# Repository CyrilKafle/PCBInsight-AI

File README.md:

# PCBInsight AI

### PCB Design Review Platform

**[View the landing page →](https://cyrilkafle.github.io/PCBInsight-AI/)**

An AI-augmented engineering design review tool for KiCad PCB projects — a lightweight, local analog of the automated design-review tooling used inside hardware companies (NVIDIA, AMD, Apple, Intel). It does not replace KiCad's Design Rule Check (DRC); it sits a level above DRC, producing the kind of higher-level engineering judgment an experienced PCB reviewer would give in a design review: *why* something could be a problem, *what engineering principle* is involved, a *suggested fix*, a *severity*, and a *confidence level*.

Full design rationale, phased plan, and engineering-check catalogue: [`DESIGN.md`](DESIGN.md). Why the major architectural calls were made the way they were: [`docs/ENGINEERING_DECISIONS.md`](docs/ENGINEERING_DECISIONS.md). How the deterministic engine and the AI layer are each validated: [`docs/VALIDATION.md`](docs/VALIDATION.md).

## Status: Phase 4 complete — full local dashboard (FastAPI + React) with board visualization, AI chat, and PDF export

This is a from-scratch rebuild of what was previously a separate FPGA/PCB robotic-arm project. See [`DESIGN.md`](DESIGN.md) for the full phased plan and [`SKILLS_LOG.md`](SKILLS_LOG.md) for tools/concepts learned as the project progresses.

## What it does

1. **Parse** — drag-and-drop a full KiCad project (`.kicad_pcb`, `.kicad_sch`, netlist, project metadata); the parser builds an internal representation of components, nets, traces, vias, copper pours, footprints, and board dimensions.
2. **Analyze** — run dozens of deterministic engineering checks across routing, power, ground integrity, differential pairs, decoupling placement, component placement, manufacturability, thermal risk, and signal integrity.
3. **AI review** — send a *summarized structured digest* of the board (never raw PCB files) to Claude for a senior-engineer-style narrative review that explains and contextualizes what the deterministic checks found.
4. **Score** — compute an overall 0-100 engineering score plus subscores (routing, power, signal integrity, manufacturability, placement, thermals, documentation), color-coded green/yellow/orange/red.
5. **Report** — generate a professional HTML report (exportable to PDF) with an executive summary, board statistics, engineering metrics, warnings, recommendations, the AI review, and charts/visualizations.

## Screenshots

Real output from a live run against `examples/stm32_usb_dev` — including a real Claude review and a real grounded chat answer, not mockups.

<table>
<tr>
<td width="50%"></td>
<td width="50%"></td>
</tr>
<tr>
<td width="50%"></td>
<td width="50%"></td>
</tr>
</table>

More screenshots (PDF export, upload flow) on the [landing page](https://cyrilkafle.github.io/PCBInsight-AI/).

## Architecture

```
backend/    FastAPI service + CLI: parser, analysis engine, AI integration, HTML/PDF report generation
frontend/   React + TypeScript + Tailwind dashboard: upload, board visualization, issue browser, AI chat panel
examples/   Engineering Validation Corpus -- ten purpose-built KiCad boards, see examples/README.md
docs/       Architecture notes, screenshots, example reports
```

See [`DESIGN.md`](DESIGN.md) for the full architecture rationale and the catalogue of engineering checks.

## Project metrics

Real numbers, computed from the codebase as of this commit — not estimates:

| Metric | Value |
|---|---|
| Analysis categories | 9 |
| Deterministic checks | 28 |
| Unit tests (all passing, backend) | 159 |
| Lines of Python — `backend/app/` | 2,957 |
| Lines of Python — `backend/tests/` | 1,386 |
| Engineering Validation Corpus | 10 purpose-built boards, see `examples/README.md` |
| KiCad parser | Custom S-expression parser, 0 `pcbnew`/CAD dependencies |
| Supported input format | KiCad `.kicad_pcb` |
| Interfaces | CLI (`pcbinsight review`, single-board or batch-folder) and a local React/FastAPI web dashboard |
| AI model | Claude Sonnet 5 (narrative review layer only — never the analysis engine) |
| Report format | Self-contained HTML (embedded charts, no external assets) and downloadable PDF (ReportLab) |

## Running it

Both the CLI and the web dashboard are runnable today.

```sh
cd backend
pip install -r requirements.txt

# Analyze one board
python -m app.cli review ../examples/simple_board
# -> simple_board_report.html in the current directory

# Analyze every board in a folder (auto-detected batch mode)
python -m app.cli review path/to/boards/ --out reports/
# -> reports/<board-folder-name>/report.html for each, plus reports/summary.html

# Add --ai to also generate a Claude narrative review (requires ANTHROPIC_API_KEY)
python -m app.cli review ../examples/simple_board --ai

# Or install it as a real `pcbinsight` command:
pip install -e .
pcbinsight review ../examples/simple_board
```

```sh
# Web dashboard (local-only -- see DESIGN.md's "Public Positioning & Audience")

# Terminal 1: backend API
cd backend
uvicorn app.main:app --port 8000

# Terminal 2: frontend dev server
cd frontend
npm install
npm run dev
# -> open http://localhost:5173, drag in a KiCad project folder
```

## Roadmap

- **Phase 0 (done):** Hand-rolled S-expression parser for `.kicad_pcb` (no `pcbnew`/KiCad-install dependency), internal Pydantic board model, proven against an `examples/` fixture board with unit tests.
- **Phase 1 (done):** Deterministic engineering-check engine — all nine categories (routing, power, ground, differential pairs, decoupling, placement, manufacturability, thermal, signal integrity) implemented as independent `check(board) -> list[Issue]` modules, orchestrated by `app/analysis/run_all_checks`. 78 tests passing (24 parser + 54 analysis), each check proven on a synthetic bad-case board and silent on a clean one. Manufacturability intentionally covers only trace width / annular ring / via density — silkscreen-over-pad and copper-sliver checks are deferred since the board model doesn't yet capture silkscreen text geometry or full pour polygon shape.
- **Phase 2 (done):** Transparent scoring engine (`app/analysis/scoring.py` — severity-weighted deductions per subscore, overall = average) and a self-contained HTML report renderer (`app/reports/html_report.py`) with embedded matplotlib charts, color-coded score badges, and a full issues table. No AI dependency yet — see [`docs/example_report.html`](docs/example_report.html) for a real generated report off the `examples/simple_board` fixture. 93 tests passing.
- **Phase 3 (done):** AI Engineering Review Layer — `app/ai/summarizer.py` builds a structured digest (scores, a deterministically-computed evidence block, issue list, board statistics; never raw geometry) and `app/ai/review.py` sends it to Claude under a strict system prompt that forbids inventing findings and requires citing issue IDs (e.g. `PWR-004`, assigned by `run_all_checks`). Claude is a technical writer over the deterministic engine's output, never a second analysis engine. `answer_question()` grounds the (Phase 4) AI chat panel the same way. The digest carries a `schema_version`, and `find_unsupported_citations()` code-checks (not just prompt-asks) that any issue ID Claude cites actually exists, logging a warning otherwise. 115 tests passing, all using a dependency-injected fake Anthropic client — no live API key needed to prove the code is correct, since none was available in this environment. See `DESIGN.md`'s "AI Integration Architecture" section for the full spec.
- **CLI (done):** `app/cli.py` — `pcbinsight review <path>` runs the full parse → analyze → score → (optional AI) → report pipeline for one board, or auto-detects a folder of boards and batch-processes all of them into per-board reports plus a `summary.html` index. Installable as a real command via `backend/pyproject.toml`'s `[project.scripts]`. Batch mode catches per-board failures so one malformed `.kicad_pcb` doesn't abort the run. 120 tests passing.
- **Phase 4 (done):** Local-only FastAPI service (`POST /api/review` with streamed/size-capped uploads and a path-traversal guard; `POST /api/chat`; `POST /api/report/pdf`) plus a React/TypeScript dashboard: drag-and-drop/folder upload, color-coded score cards, searchable/filterable issue browser with expandable "why does this matter" detail, an **SVG board visualization** (outline, per-layer traces, vias, components, zoom/pan, layer toggles, clickable issue markers that cross-highlight the issue browser), a **net-length histogram** and **issue-by-category chart**, a **grounded AI chat panel** (reuses the Phase 3 `answer_question()`; fails gracefully without an API key), and **PDF export** (ReportLab, reusing the HTML report's charts). Verified end-to-end in a real browser against the running backend. 135 tests passing (backend).
- **Stretch:** multi-board comparison, revision history, BOM analysis, Altium/EasyEDA import support, plugin architecture (see `DESIGN.md` for the full stretch list, including the review-session workflow and Design Rule Authoring SDK).

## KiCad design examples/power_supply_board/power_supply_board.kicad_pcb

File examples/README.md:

# Engineering Validation Corpus

This is not a folder of demo files — it's a curated set of KiCad boards, each authored for a specific reason, that validates the parser, the deterministic analysis engine, the AI layer, and the dashboard end to end. Every board exists to prove something the others don't; there are no filler fixtures. See `docs/VALIDATION.md` for how to run the full validation flow (this corpus + `backend/scripts/validate_ai.py`) and how to interpret the results.

| Board | Primary purpose |
|---|---|
| `simple_board` | Parser smoke test — minimal hand-authored board exercising every S-expression construct the parser handles |
| `stm32_usb_dev` | Medium-quality realistic board — a substantial fixture for the analysis engine |
| `flawed_reference` | Deliberately poor board tripping nearly every check category at once |
| `high_quality_reference` | Clean reference board — demonstrates good engineering, the "everything's fine" counterpart to `flawed_reference` |
| `rf_clock_board` | Signal-integrity and differential-pair focus |
| `power_supply_board` | Power delivery and decoupling focus |
| `thermal_reference` | Thermal design focus |
| `manufacturing_reference` | DFM (manufacturability) focus |
| `parser_edge_cases` | Parser robustness — unicode, escaped quotes, hostile characters, not analysis-engine coverage |
| `mixed_realistic_board` | What an intermediate engineer's board actually looks like — mostly solid, a few realistic slips |

## simple_board

Hand-authored minimal two-layer board (`simple_board.kicad_pcb` + `.kicad_pro`) used as the Phase 0 parser fixture. Not a KiCad-exported file — written directly in KiCad's S-expression format to exercise every construct the parser needs to handle: board outline (`gr_rect` on `Edge.Cuts`), two copper layers, four footprints (`U1` MCU, `C1` decoupling cap, `R1` resistor, `J1` USB-C connector) covering the refdes-prefix classification table, three nets (`GND`, `+3V3`, `/SCLK`) with traces, a via, and a `GND` copper pour zone.

## stm32_usb_dev

A richer four-layer example board (`stm32_usb_dev.kicad_pcb` + `.kicad_pro`) — an STM32F103 USB dev board: MCU, AMS1117-3.3 LDO, 8&nbsp;MHz crystal with load caps, USB-C connector with a D+/D− pair and series resistors, an SWD header, decoupling caps, an LED, and GND / +3V3 / GND power-and-ground pours across the inner and back copper layers (18 components, 12 nets). It exists to exercise the analysis engine on a more substantial board than `simple_board` — PCBInsight scores it 98/100 with 8 findings across routing, power, and decoupling (a thin +3V3 trace, a decoupling cap placed a little far from the MCU, and several low-confidence dangling-trace-end warnings from partial routing).

> **AI-generated example board.** This `.kicad_pcb` was authored with AI assistance as synthetic test/demo data for the analyzer — not a hand-routed, fab-ready design and not a substitute for real KiCad layout work. It is intentionally only partially routed. Treat it as example input for the tool, not as reference PCB design.

## flawed_reference

A deliberately low-quality two-layer board (`flawed_reference.kicad_pcb` + `.kicad_pro`) — same STM32/USB/LDO component set as `stm32_usb_dev`, but routed to trip nearly every check category at once: acute-angle trace bends, thin power/ground traces (0.15mm), two disconnected ground nets with no copper pour on either, a decoupling cap placed tens of mm from the ICs it should serve, a regulator with no decoupling cap on its input net at all, undersized via annular rings, no thermal relief pour near the regulator, and an unnecessarily long/via-heavy clock net. PCBInsight scores it 83/100 with 24 findings across all 7 active check categories (routing, power, ground, decoupling, manufacturability, thermal, signal integrity) — this is the board to reach for when demonstrating that the tool actually catches problems, not just when it says everything's fine.

> **AI-generated example board.** Same caveat as `stm32_usb_dev` above: synthetic test/demo data, not a real design (in this case, deliberately a bad one on purpose).

## high_quality_reference

A clean two-layer board (`high_quality_reference.kicad_pcb` + `.kicad_pro`) — USB-C input, LM1117-3.3 regulator, STM32 MCU — routed and decoupled correctly: adequately wide power/ground traces, every IC's power pin has a decoupling cap within the recommended distance, a full ground pour, no acute-angle bends, and a connector placed at the board edge. PCBInsight scores it **100/100 with zero findings**. This is the deliberate counterpart to `flawed_reference`: proof the tool doesn't just find problems, it also correctly recognizes when there aren't any.

> **AI-generated example board.** Synthetic test/demo data, authored with AI assistance to hit exact deterministic-check thresholds cleanly.

## rf_clock_board

A two-layer board (`rf_clock_board.kicad_pcb` + `.kicad_pro`) built around an STM32 MCU driving a clock net and a `DATA_P`/`DATA_N` differential pair to a USB-C connector, purpose-built to trip the signal-integrity and differential-pair checks specifically: the clock net is routed through a three-way branch point, uses three vias (over the two-via warning threshold), and totals 58mm (over the 40mm warning length) — three separate signal-integrity findings. The differential pair is routed with mismatched lengths (8.1mm skew), asymmetric via count (one leg has a via, the other doesn't), and a segment-count mismatch (1 segment vs. 4) — three separate differential-pair findings. Power, ground, decoupling, and placement are all kept clean so these two categories are the whole story. PCBInsight scores it 98/100 with 7 findings (6 SI/diff-pair, 1 incidental low-confidence dangling-stub note from the branch).

> **AI-generated example board.** Synthetic test/demo data, authored with AI assistance to hit exact deterministic-check thresholds cleanly.

## power_supply_board

A two-layer board (`power_supply_board.kicad_pcb` + `.kicad_pro`) — USB-C input, LM1117-3.3 regulator, STM32 MCU load — purpose-built around power-delivery and decoupling mistakes: the regulator has no decoupling capacitor at all on its +5V input net (a missing-decoupling finding), a capacitor exists for the +3V3 output but is placed 10mm away — well past the recommended distance (a too-far finding), the +5V supply trace is 0.20mm (below the 0.30mm guideline), there's no ground copper pour anywhere on the board, and consequently no thermal relief near the regulator either. PCBInsight scores it 96/100 with 5 findings spanning decoupling, power, ground, and thermal — a realistic cluster of power-subsystem oversights rather than a single isolated defect.

> **AI-generated example board.** Synthetic test/demo data, authored with AI assistance to hit exact deterministic-check thresholds cleanly.

## thermal_reference

A two-layer board (`thermal_reference.kicad_pcb` + `.kicad_pro`) — LM1117-3.3 regulator and an N-MOSFET placed close together, both correctly decoupled, with a ground pour present on the board but positioned nowhere near either heat source. This isolates the thermal category cleanly: no copper pour within range of the regulator, no copper pour within range of the MOSFET, and the two heat sources are close enough together (5.4mm) to compound each other's thermal rise. PCBInsight scores it 99/100 with exactly 3 findings, all thermal.

> **AI-generated example board.** Synthetic test/demo data, authored with AI assistance to hit exact deterministic-check thresholds cleanly.

## manufacturing_reference

A tiny two-layer board (`manufacturing_reference.kicad_pcb` + `.kicad_pro`, 12mm × 12mm) built to trip every manufacturability (DFM) check: a 0.10mm trace segment (below the 0.15mm fab-minimum), two vias with a 0.025mm annular ring (below the 0.075mm fab-minimum), and eight stitching vias packed into the small board area to push via density over 5/cm². The dense via cluster also trips routing's excessive-via-count check on that net — a realistic secondary effect of the same root cause, not a separate story. PCBInsight scores it 95/100 with 6 findings, 4 of them manufacturability.

> **AI-generated example board.** Synthetic test/demo data, authored with AI assistance to hit exact deterministic-check thresholds cleanly.

## parser_edge_cases

A small two-layer board (`parser_edge_cases.kicad_pcb` + `.kicad_pro`) that exists to stress the **parser**, not the analysis engine — deliberately hostile but valid KiCad S-expression text: a component value with an escaped quote and a Greek letter (`Cap_100nF \"X7R\" Ω`), a net name with angle brackets (`VCC<3V3>`), unicode characters mixed into both a net name and a reference designator (`R&D_信号`, `J-长`), an ampersand and hyphen inside a reference designator, parentheses embedded inside a quoted net name, a ~90-character net name, and a lowercase reference designator (`u1`) to confirm case-insensitive component classification. All of it parses cleanly and classifies correctly — verified directly against the parsed `Board` object, not just "the CLI didn't crash."

> **AI-generated example board.** Synthetic test/demo data, authored with AI assistance specifically to exercise string/tokenizer edge cases.

## mixed_realistic_board

A two-layer board (`mixed_realistic_board.kicad_pcb` + `.kicad_pro`) meant to look like what an intermediate engineer actually ships — not a showcase of best practices (`high_quality_reference`) and not a pile of violations (`flawed_reference`). Power delivery, grounding, and most decoupling are done correctly; the realistic slips are a single decoupling cap placed too far from its MCU, one clock net that ran a bit longer than ideal (47mm, no other clock issues), one isolated trace segment that came in under the manufacturing minimum, and one incidental dangling-stub note. PCBInsight scores it 98/100 with 4 findings spread across four different categories — the board to reach for when you want "good work with a couple of real mistakes," not either extreme.

> **AI-generated example board.** Synthetic test/demo data, authored with AI assistance to hit exact deterministic-check thresholds cleanly.

---

Per `DESIGN.md`'s open questions, the fixture set should keep growing to include additional clean reference boards plus at least one intentionally-flawed board per check category — this corpus now covers that for the current check set, split into ten purpose-built boards rather than one board doing everything.

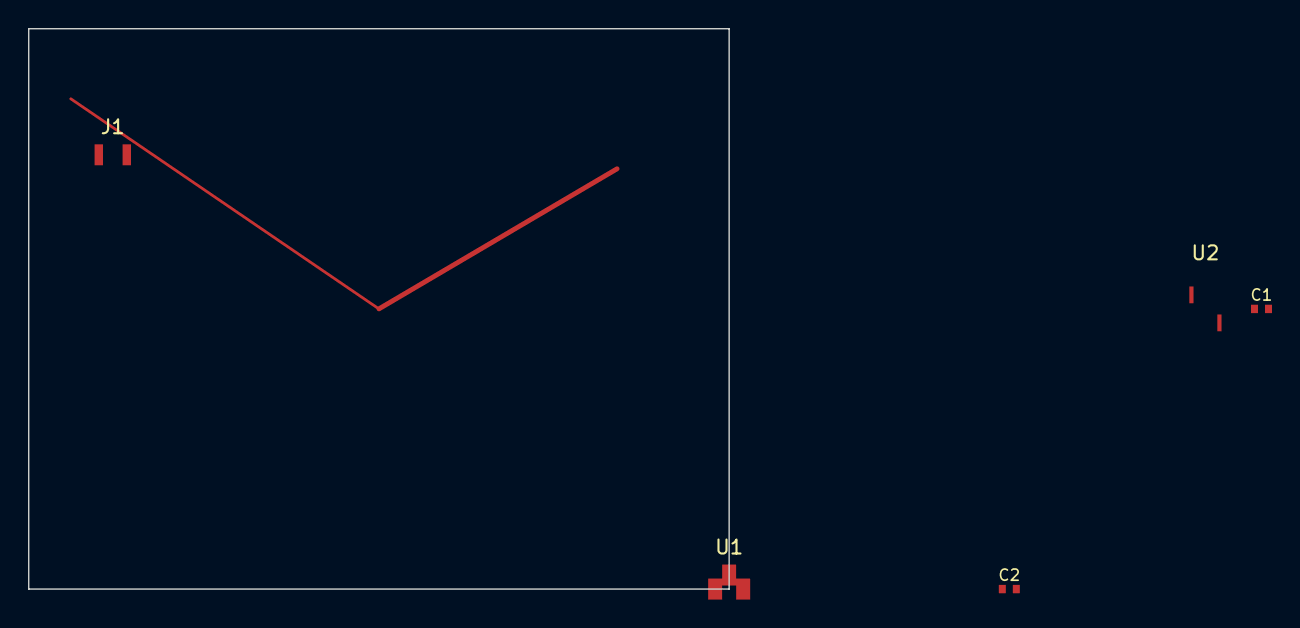
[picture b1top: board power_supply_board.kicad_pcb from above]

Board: 2 copper layers, 50.0 x 40.0 mm, 5 parts (0 on the bottom side), 3 nets.

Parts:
C1: 100nF; C_0402_1005Metric
C2: 10uF; C_0402_1005Metric
J1: USB_C; USB_C_Receptacle
U1: LM1117-3.3; SOT-223-3_TabPin2
U2: STM32F103C8T6; LQFP-48_7x7mm_P0.5mm

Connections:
+3V3: C1.1, C2.1, U1.2, U2.8
+5V: J1.VBUS, U1.3
GND: C1.2, C2.2, J1.GND, U1.1, U2.23

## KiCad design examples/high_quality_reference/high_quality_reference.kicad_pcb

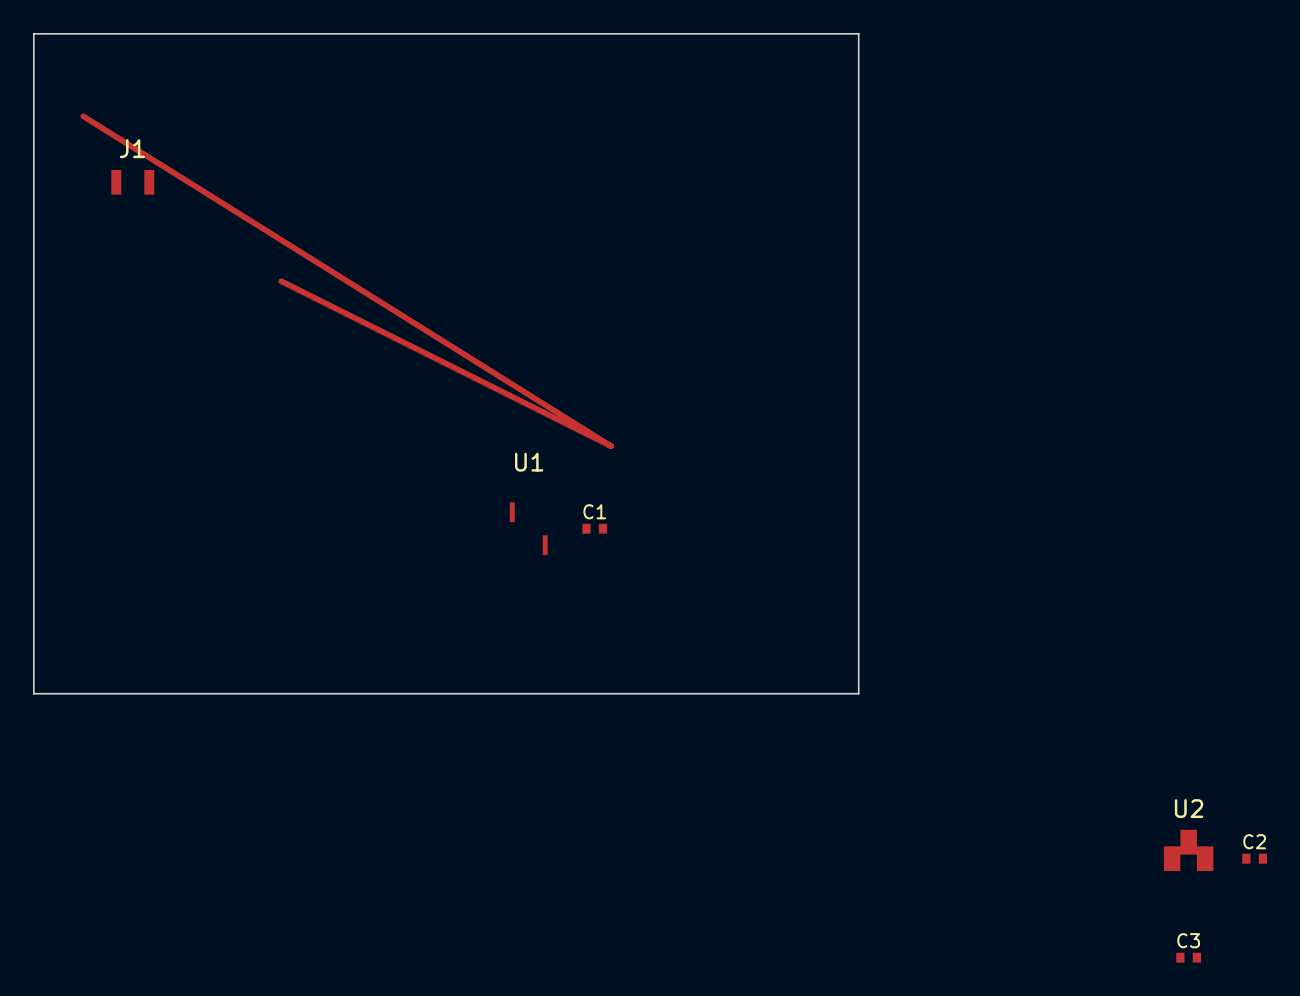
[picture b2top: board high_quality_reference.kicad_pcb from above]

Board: 2 copper layers, 50.0 x 40.0 mm, 6 parts (0 on the bottom side), 3 nets.

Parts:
C1, C2: 100nF; C_0402_1005Metric
C3: 10uF; C_0402_1005Metric
J1: USB_C; USB_C_Receptacle
U1: STM32F103C8T6; LQFP-48_7x7mm_P0.5mm
U2: LM1117-3.3; SOT-223-3_TabPin2

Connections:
+3V3: C1.1, C2.1, U1.8, U2.2
+5V: C3.1, J1.VBUS, U2.3
GND: C1.2, C2.2, C3.2, J1.GND, U1.23, U2.1

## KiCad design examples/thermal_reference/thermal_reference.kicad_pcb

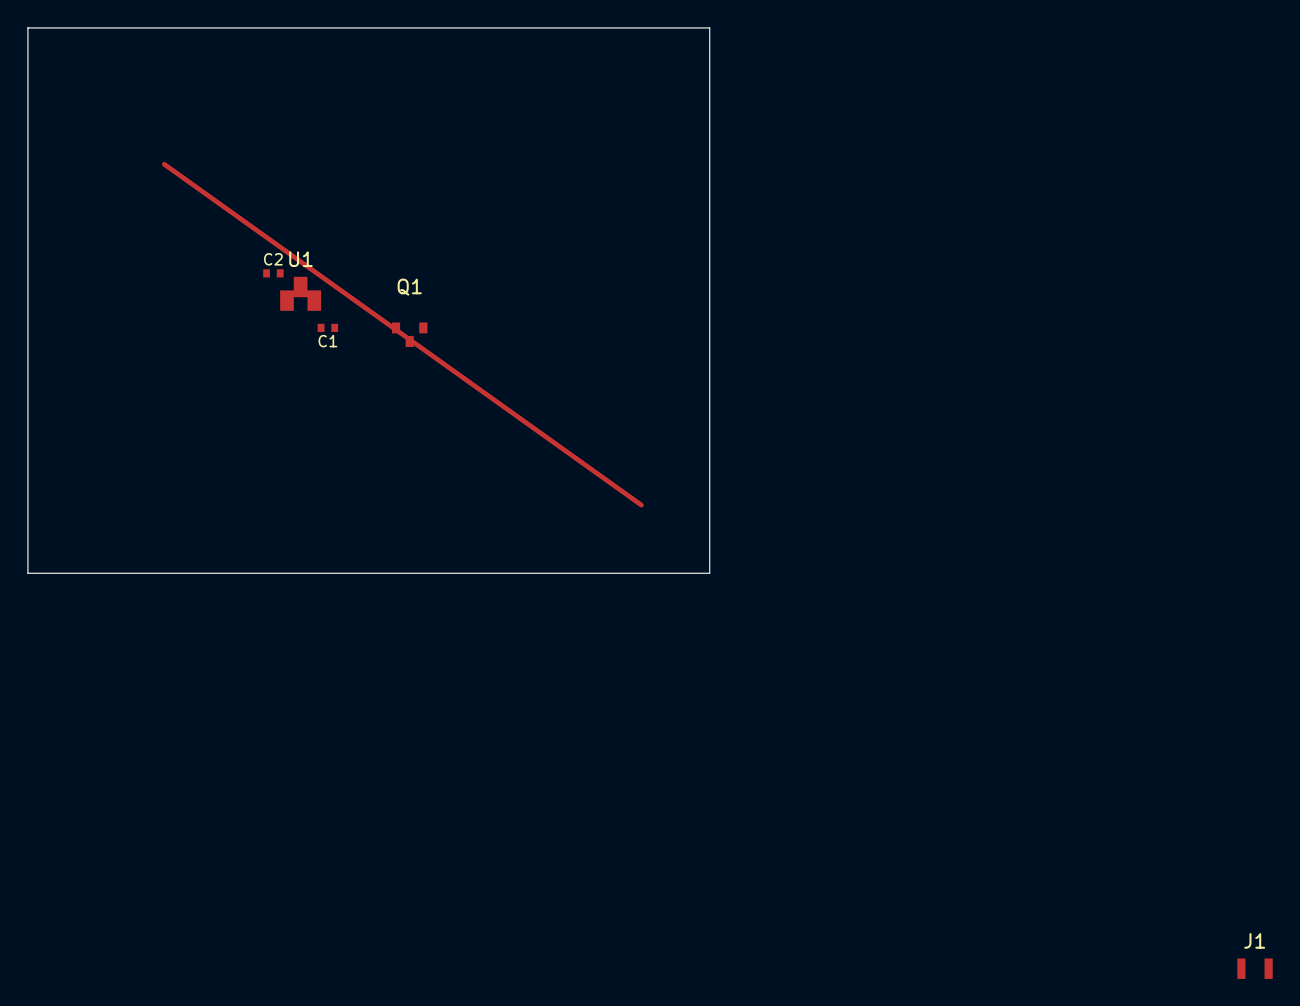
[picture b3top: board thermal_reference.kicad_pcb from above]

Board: 2 copper layers, 50.0 x 40.0 mm, 5 parts (0 on the bottom side), 3 nets.

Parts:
C1: 100nF; C_0402_1005Metric
C2: 10uF; C_0402_1005Metric
J1: USB_C; USB_C_Receptacle
Q1: IRLZ44N (N-MOSFET); SOT-23
U1: LM1117-3.3; SOT-223-3_TabPin2

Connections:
+3V3: C1.1, U1.2
+5V: C2.1, J1.VBUS, U1.3
GND: C1.2, C2.2, J1.GND, Q1.2, U1.1

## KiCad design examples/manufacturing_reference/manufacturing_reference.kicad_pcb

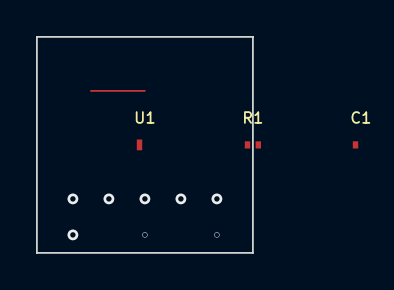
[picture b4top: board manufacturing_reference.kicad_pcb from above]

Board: 2 copper layers, 12.0 x 12.0 mm, 3 parts (0 on the bottom side), 2 nets.

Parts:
C1: 100nF; C_0402_1005Metric
R1: 1k; R_0402_1005Metric
U1: 74HC04; SOIC-14_3.9x8.7mm_P1.27mm

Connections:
SIG1: R1.1, U1.1
STITCH: C1.1, R1.2

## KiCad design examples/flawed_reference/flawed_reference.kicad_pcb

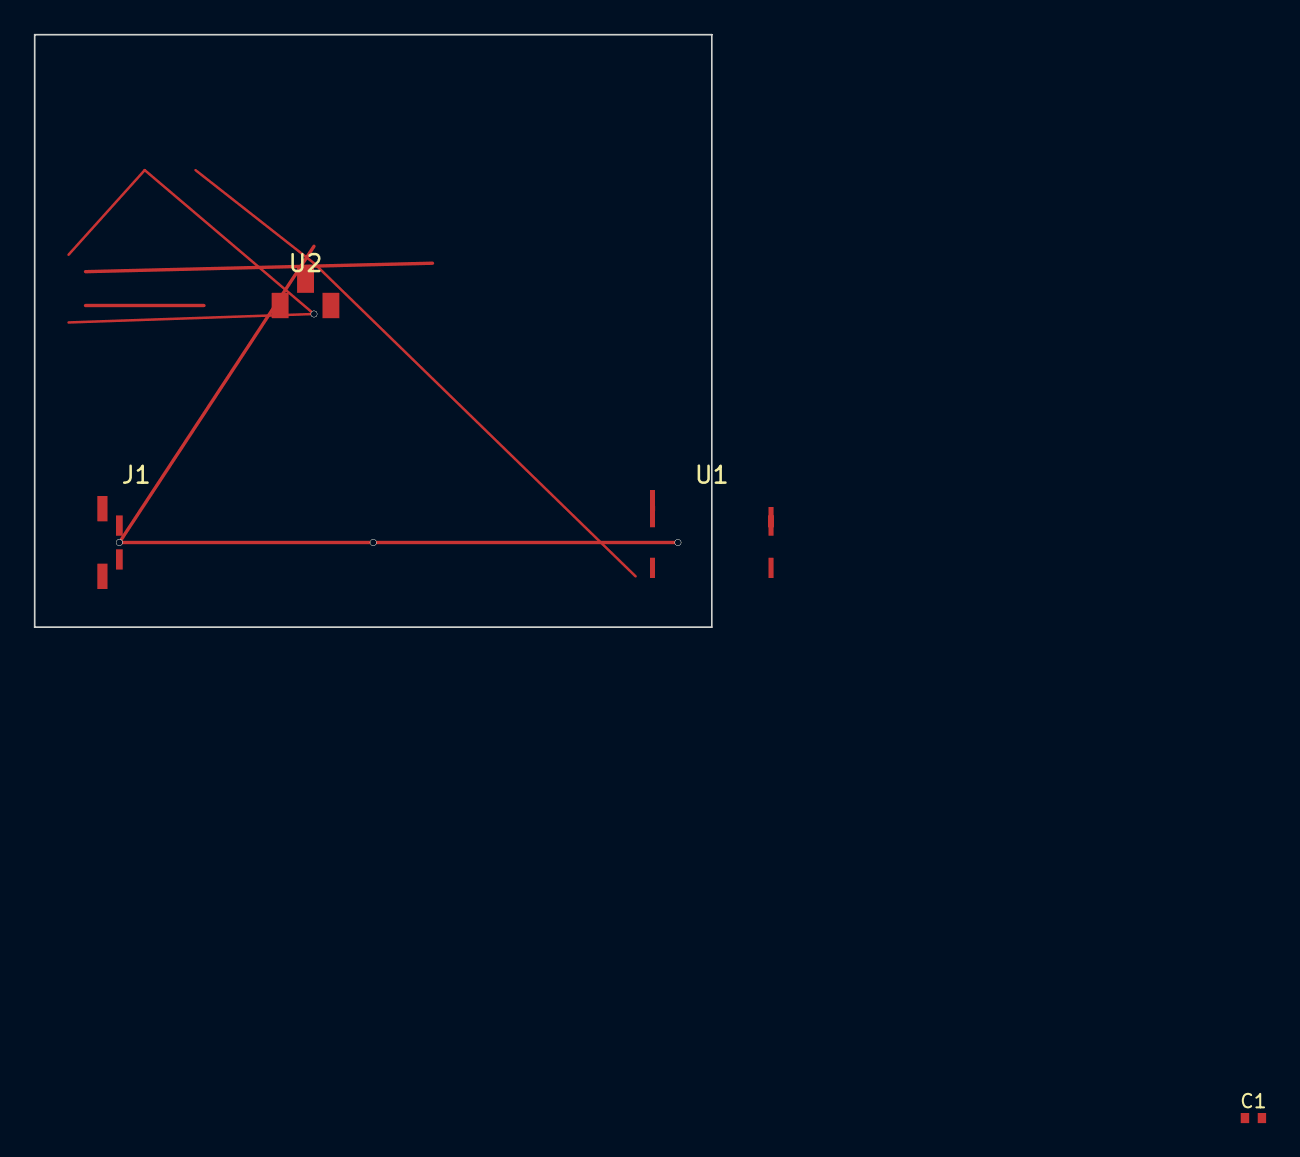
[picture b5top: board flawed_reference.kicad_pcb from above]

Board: 2 copper layers, 40.0 x 35.0 mm, 4 parts (0 on the bottom side), 5 nets.

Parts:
C1: 100nF; C_0402_1005Metric
J1: USB_C; USB_C_Receptacle_GCT_USB4085
U1: STM32F103C8T6; LQFP-48_7x7mm_P0.5mm
U2: LM1117-3.3; SOT-223-3_TabPin2

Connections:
+3V3: C1.1, U1.8, U2.2
+5V: J1.VBUS, U2.3
/USB_DM: J1.DM, U1.43
/USB_DP: J1.DP, U1.44
GND: C1.2, U1.23, U2.1

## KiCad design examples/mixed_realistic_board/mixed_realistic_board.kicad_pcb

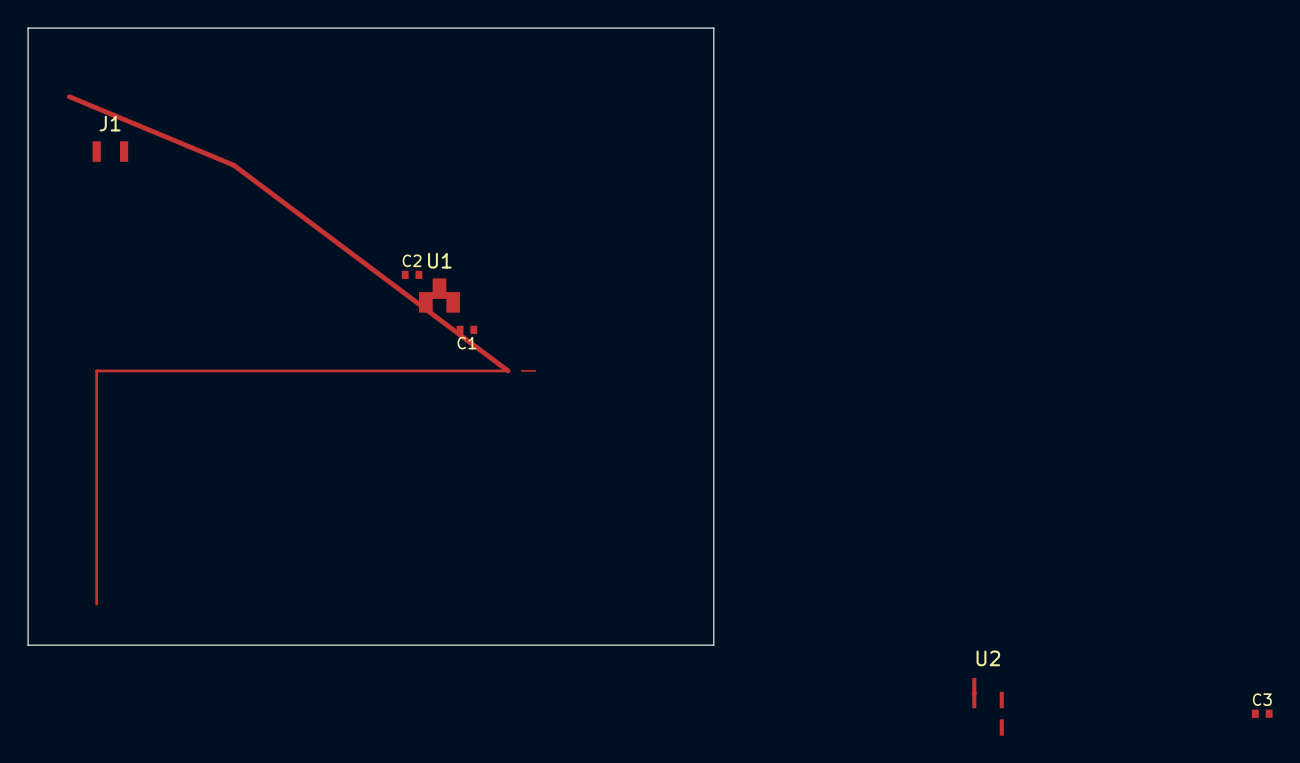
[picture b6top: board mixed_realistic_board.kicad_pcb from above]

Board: 2 copper layers, 50.0 x 45.0 mm, 6 parts (0 on the bottom side), 3 nets.

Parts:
C1, C3: 100nF; C_0402_1005Metric
C2: 10uF; C_0402_1005Metric
J1: USB_C; USB_C_Receptacle
U1: LM1117-3.3; SOT-223-3_TabPin2
U2: STM32F103C8T6; LQFP-48_7x7mm_P0.5mm

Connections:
+3V3: C1.1, C3.1, U1.2, U2.8
+5V: C2.1, J1.VBUS, U1.3
GND: C1.2, C2.2, C3.2, J1.GND, U1.1, U2.23

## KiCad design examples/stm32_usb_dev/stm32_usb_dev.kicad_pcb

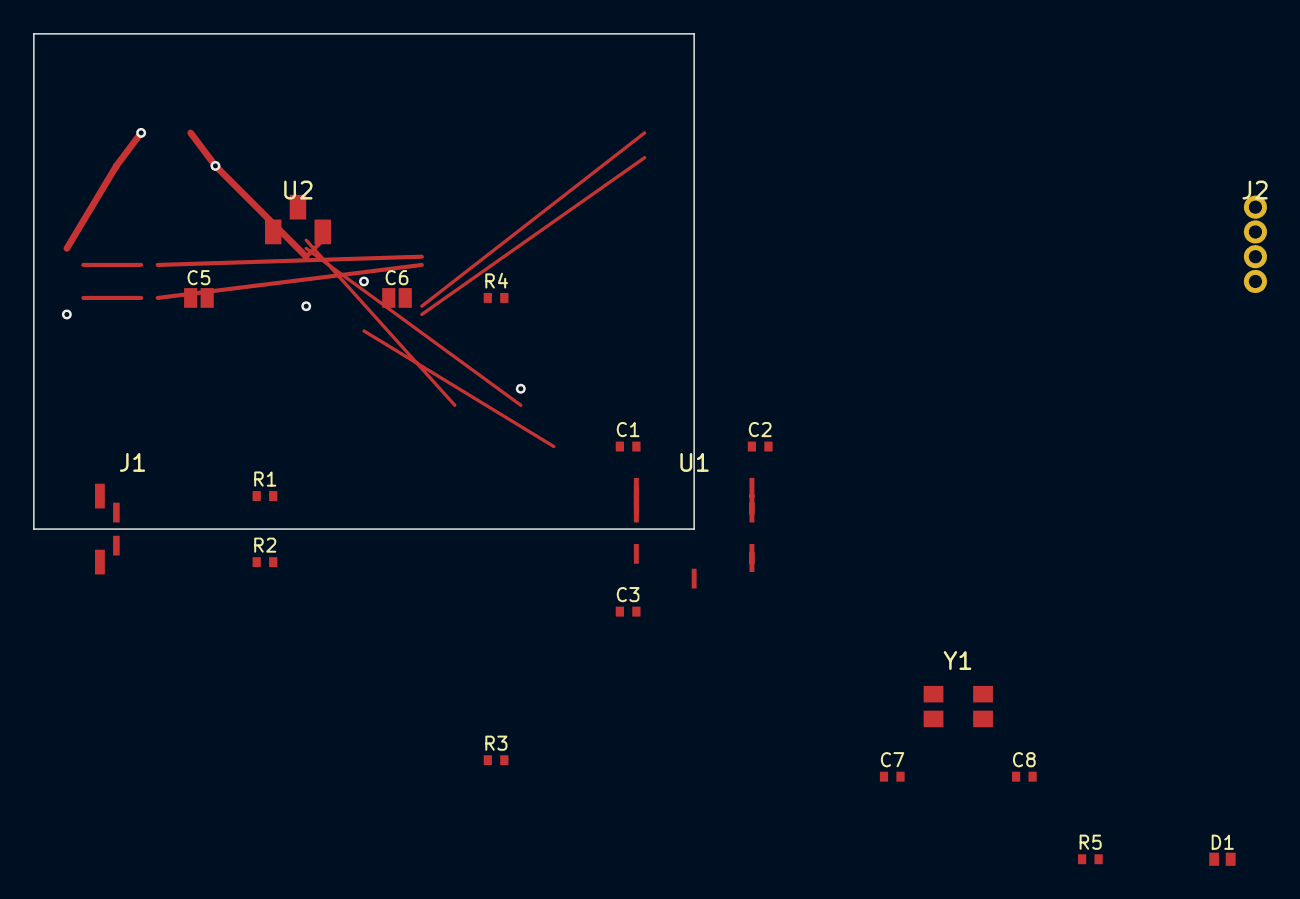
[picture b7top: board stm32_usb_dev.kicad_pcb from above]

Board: 4 copper layers, 40.0 x 30.0 mm, 18 parts (0 on the bottom side), 12 nets.

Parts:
C1, C2, C3: 100nF; C_0402_1005Metric
C5, C6: 10uF; C_0805_2012Metric
C7, C8: 22pF; C_0402_1005Metric
D1: LED; LED_0603_1608Metric
J1: USB_C; USB_C_Receptacle_GCT_USB4085
J2: SWD; PinHeader_1x04_P2.54mm_Vertical
R1, R2: 22R; R_0402_1005Metric
R3, R4: 10k; R_0402_1005Metric
R5: 1k; R_0402_1005Metric
U1: STM32F103C8T6; LQFP-48_7x7mm_P0.5mm
U2: AMS1117-3.3; SOT-223-3_TabPin2
Y1: 8MHz; Crystal_SMD_3225-4Pin_3.2x2.5mm

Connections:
+3V3: C1.1, C2.1, C3.1, C6.1, D1.1, J2.1, R4.2, U1.8, U2.2
+5V: C5.1, J1.VBUS, U2.3
/BOOT0: R3.1, U1.44b
/LED: D1.2, R5.1, U1.20
/NRST: R4.1, U1.7
/SWCLK: J2.3, U1.37
/SWDIO: J2.2, U1.34
/USB_DM: J1.DM, R2.1, R2.2, U1.43
/USB_DP: J1.DP, R1.1, R1.2, U1.44
/XTAL_IN: C7.1, U1.5, Y1.1
/XTAL_OUT: C8.1, U1.6, Y1.2
GND: C1.2, C2.2, C3.2, C5.2, C6.2, C7.2, C8.2, J1.GND, J2.4, R3.2, R5.2, U1.23, U2.1, Y1.3, Y1.4

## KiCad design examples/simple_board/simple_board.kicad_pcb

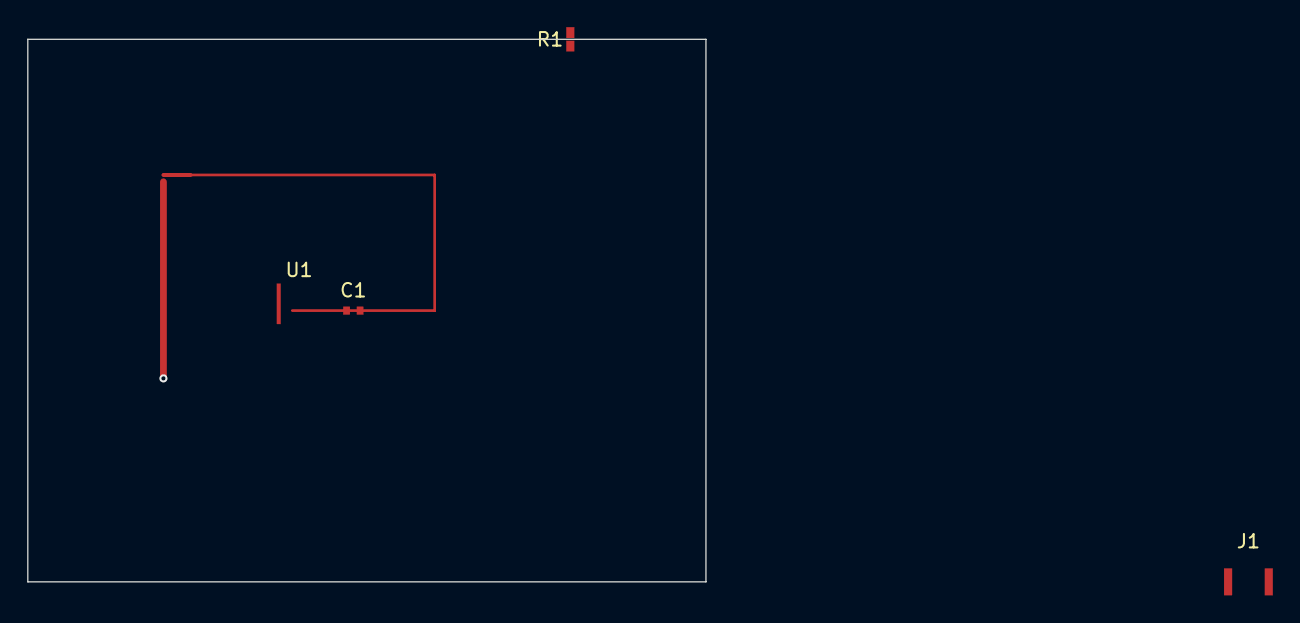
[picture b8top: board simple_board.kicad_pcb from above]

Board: 2 copper layers, 50.0 x 40.0 mm, 4 parts (0 on the bottom side), 3 nets.

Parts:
C1: 100nF; C_0402_1005Metric
J1: USB_C; USB_C_Receptacle
R1: 10k; R_0603_1608Metric
U1: ATmega328P-AU; TQFP-32_7x7mm_P0.8mm

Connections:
+3V3: C1.1, J1.1, U1.1
/SCLK: R1.1, U1.3
GND: C1.2, J1.2, R1.2, U1.2

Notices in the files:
README.md:
License: MIT
